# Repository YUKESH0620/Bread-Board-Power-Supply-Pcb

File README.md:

# Bread Board Power Supply (KiCad 9)

Compact breadboard-compatible power supply PCB designed in KiCad 9 for quick prototyping on standard solderless breadboards.

## Status
- KiCad version: 9.0
- Prototype status: Prototype built
- Files included: schematics, PCB layout, Gerbers, BOM, documentation

## Preview

## Key features
- Breadboard-compatible footprint
- 5V Output voltage
- Adjustable or additional rails:3.3 V 
- Short-circuit / thermal protection
- Compact form factor suitable for prototyping

## Specifications
- Input voltage: 7–12 V DC
- Output voltage(s): 5 V, 3.3 V
- Maximum output current:up to 1 A
- Board dimensions:51.65mm×32.25mm
- Connector types: DC barrel Jack connector(Female)

## Repository layout
- Bread_Board_Power_Supply001.kicad_pro  — KiCad project file
- Bread_Board_Power_Supply001.kicad_sch  — Schematic
- Bread_Board_Power_Supply001.kicad_pcb  — PCB layout
- Gerber_Files/                          — Gerber files for fabrication
- LICENSE                                — Project license (see LICENSE file)
- README.md                              — This file

## Getting started
1. Install KiCad 9.0.0 and open Bread_Board_Power_Supply001.kicad_pro.
2. Review the schematic and footprints; verify design rules.
3. Generate fabrication files: File → Plot (Gerber) and drill files.
4. Inspect BOM located in the repository.

## Manufacturing & assembly
- Gerbers: check Gerber_Files/ before sending to your PCB house.
- BOM: add part numbers, package types and vendor links in the BOM folder.
- Assembly notes:
  - Follow polarity markings for electrolytic capacitors, diodes, and regulators.
  - Hand-solder or use reflow for SMDs depending on your workflow.

## Testing procedure
1. Visual inspection for solder bridges and component orientation.
2. Continuity test between power rails and ground.
3. Power the board with a current-limited supply and verify output voltages with a multimeter before connecting loads.
4. Verify thermal behavior under expected load.
5. Record test results in docs/test-report.md.

## Safety & disclaimer
- Use appropriate current limiting when powering a newly assembled board.
- Confirm correct polarity of the input connector.
- This design is provided as-is. The author is not responsible for damage from improper use. Verify suitability for your application.

## Contributing
Contributions are welcome. Please:
1. Fork the repository.
2. Create a descriptive feature branch.
3. Submit a pull request with a detailed explanation of changes and test results.

When contributing PCB changes, include updated KiCad files, BOM updates, and test logs.

## License
See the LICENSE file in this repository for license details.

## Contact
Maintainer: YUKESH0620
GitHub: https://github.com/YUKESH0620

## Changelog
- v0.1 — Initial KiCad 9 design and repository (update as needed)

---

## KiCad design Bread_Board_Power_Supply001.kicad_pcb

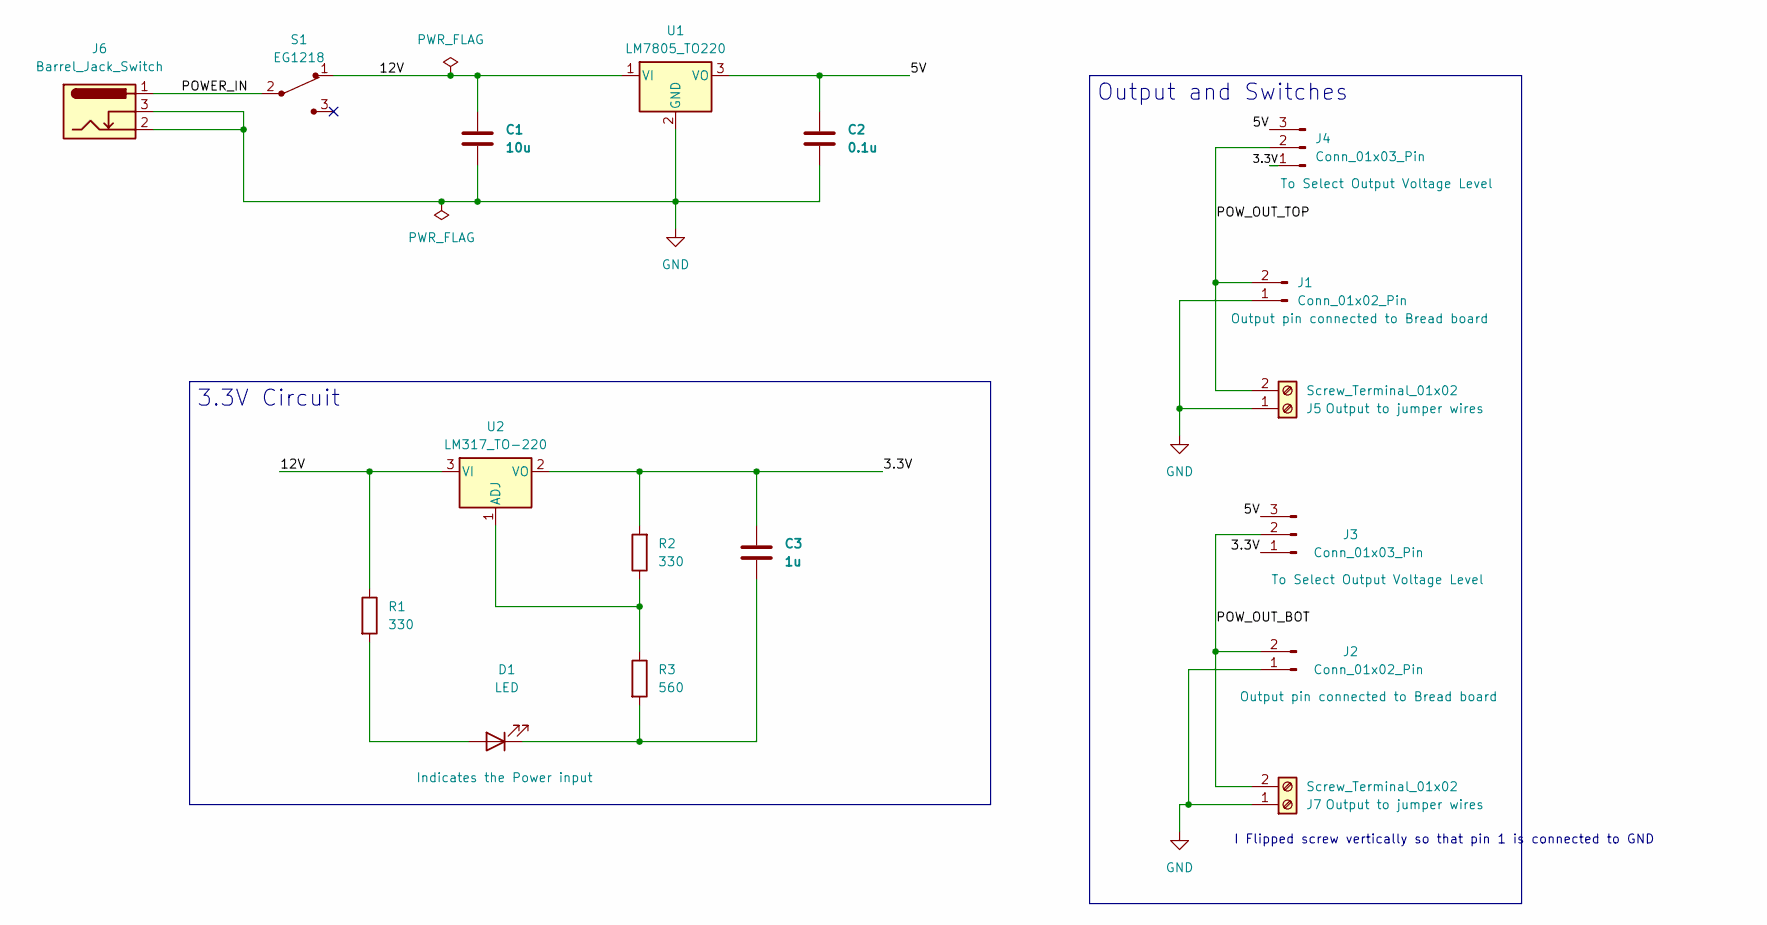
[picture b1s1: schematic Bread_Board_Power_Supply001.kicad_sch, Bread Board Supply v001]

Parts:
C1: 10u; C_Disc_D5.0mm_W2.5mm_P2.50mm
C2: 0.1u; C_Disc_D5.0mm_W2.5mm_P2.50mm
C3: 1u; C_Disc_D5.0mm_W2.5mm_P2.50mm
D1: LED; LED_D5.0mm
J1, J2: Conn_01x02_Pin; PinHeader_1x02_P2.54mm_Vertical
J3, J4: Conn_01x03_Pin; PinHeader_1x03_P2.54mm_Vertical
J5, J7: Screw_Terminal_01x02; TerminalBlock_bornier-2_P5.08mm
J6: Barrel_Jack_Switch; BarrelJack_Horizontal
R1, R2: 330; R_Axial_DIN0204_L3.6mm_D1.6mm_P2.54mm_Vertical
R3: 560; R_Axial_DIN0204_L3.6mm_D1.6mm_P2.54mm_Vertical
S1: EG1218; Switch_Slide_11.6x4mm_EG1218; MPN EG1218; Digi-Key_PN EG1903-ND
U1: LM7805_TO220; TO-220-3_Vertical
U2: LM317_TO-220; TO-220-3_Vertical

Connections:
/3.3V: C3.1, J3.1, J4.1, R2.2, U2.2 (VO)
/5V: C2.1, J3.3, J4.3, U1.3 (VO)
/12V: C1.1, R1.1, S1.1, U1.1 (VI), U2.3 (VI)
/POWER_IN: J6.1, S1.2
/POW_OUT_BOT: J2.2, J3.2, J7.2
/POW_OUT_TOP: J1.2, J4.2, J5.2
GND: C1.2, C2.2, J1.1, J2.1, J5.1, J6.2, J6.3, J7.1, U1.2 (GND)
unnamed: D1.2 (A), R1.2
unnamed: C3.2, D1.1 (K), R3.2
unnamed: R2.1, R3.1, U2.1 (ADJ)

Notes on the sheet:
I Flipped screw vertically so that pin 1 is connected to GND
Output and Switches
3.3V Circuit

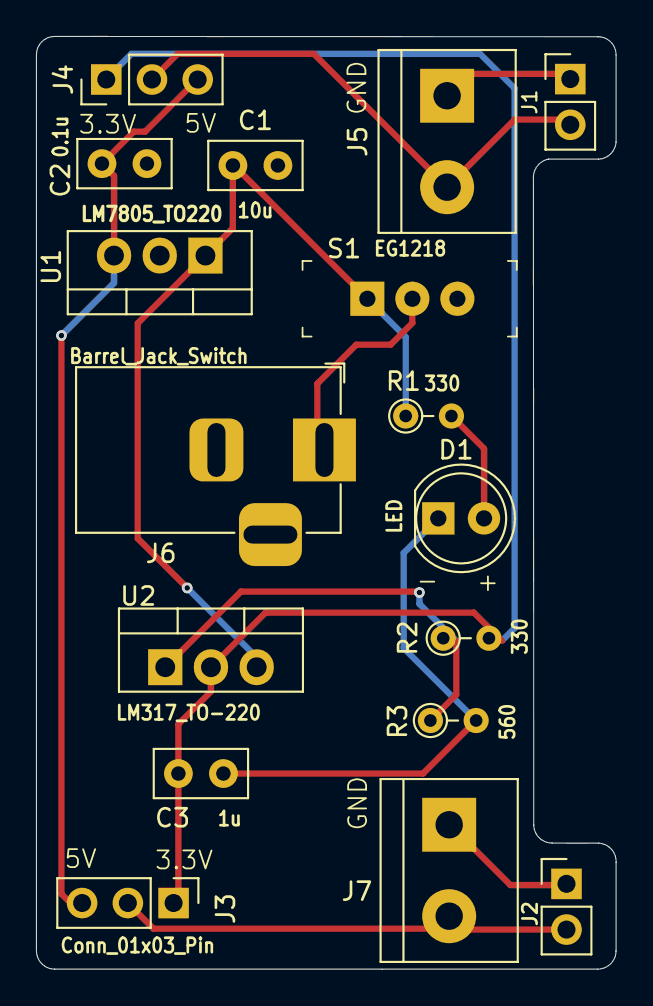
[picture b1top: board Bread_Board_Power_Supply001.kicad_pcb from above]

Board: 2 copper layers, 32.2 x 51.8 mm, 17 parts (0 on the bottom side), 10 nets.

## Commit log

2025-12-06 Revise README for Breadboard Power Supply PCB project
    Updated README to provide detailed project information, including motivation, features, learning outcomes, and future improvements.
2025-12-06 Fix formatting in README.md for key features
    Removed space after the bullet point for dual regulated outputs.
2025-12-06 Update README with project details and images
2025-12-06 Gerber files
2025-12-08 docs: add professional README (placeholders left to fill)
2025-12-09 Revise specifications and KiCad installation version
    Updated specifications and installation instructions in README.
